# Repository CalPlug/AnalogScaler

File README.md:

# AnalogScaler
This circuit uses two quad operational amplifiers to scale a bi-polar input signal to be sampled by a 0-3.3V ADC that is common on microcontrollers

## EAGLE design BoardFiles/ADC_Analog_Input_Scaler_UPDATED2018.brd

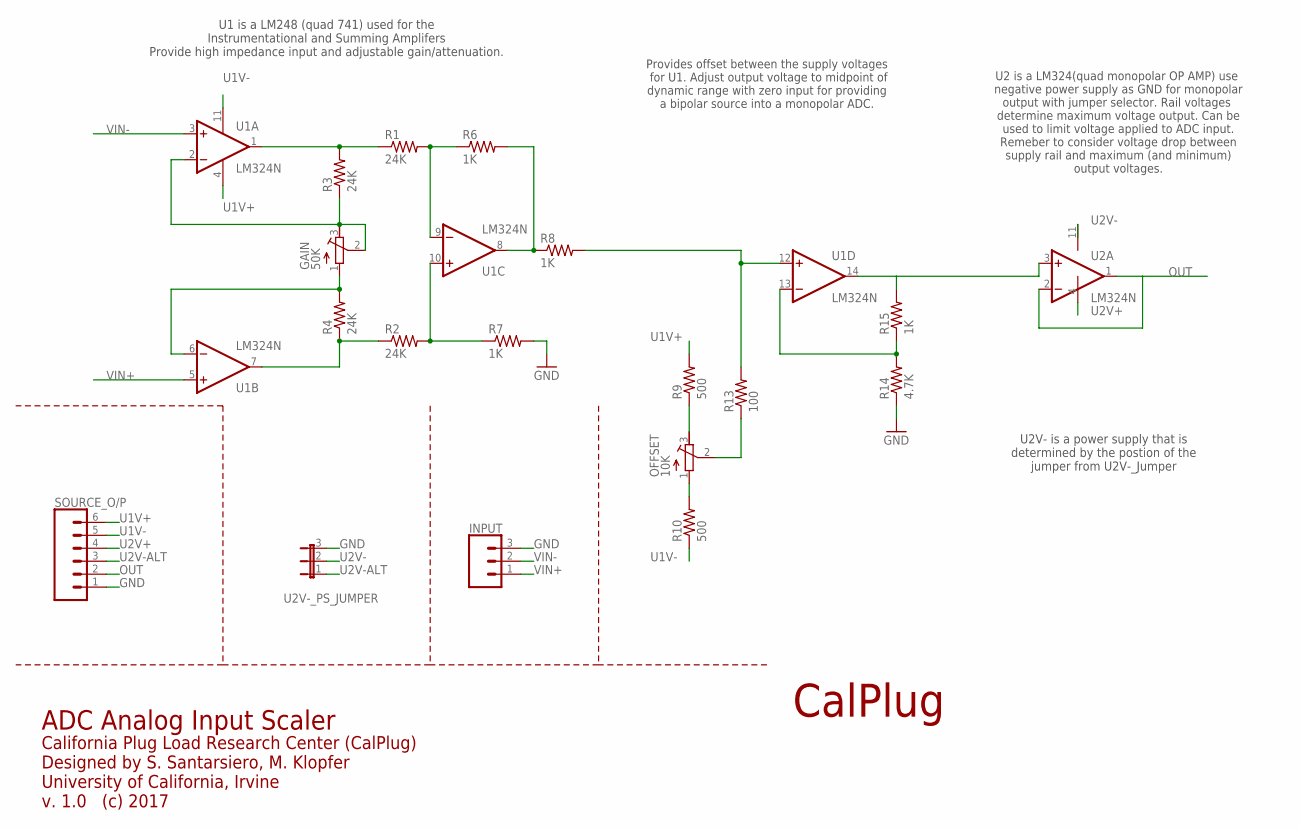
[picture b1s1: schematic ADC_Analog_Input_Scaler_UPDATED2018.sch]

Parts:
GAIN: 50K; RTRIM3296W
INPUT: CONN_03; 1X03
OFFSET: 10K; RTRIM3296W
R1, R2, R3, R4: 24K; R1210
R6, R7, R8, R15: 1K; R1210
R9, R10: 500; R1206
R13: 100; R1210
R14: 4.7K; R1210
SOURCE_O/P: CONN_06LOCK; 1X06_LOCK
U1, U2: LM324N; DIL14
U2V-_PS_JUMPER: JP2E; JP2

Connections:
GND: INPUT.3, R7.2, R14.1, SOURCE_O/P.1, U2V-_PS_JUMPER.3
unnamed: GAIN.1 (A), R4.2, U1.6 (-IN)
unnamed: R1.1, R3.2, U1.1 (OUT)
unnamed: R2.1, R4.1, U1.7 (OUT)
unnamed: R1.2, R6.1, U1.9 (-IN)
unnamed: OFFSET.1 (A), R10.2
unnamed: R6.2, R8.1, U1.8 (OUT)
unnamed: R2.2, R7.1, U1.10 (+IN)
unnamed: OFFSET.3 (E), R9.1
unnamed: GAIN.2 (S), GAIN.3 (E), R3.1, U1.2 (-IN)
unnamed: R8.2, R13.2, U1.12 (+IN)
unnamed: OFFSET.2 (S), R13.1
unnamed: R15.2, U1.14 (OUT), U2.3 (+IN)
unnamed: R14.2, R15.1, U1.13 (-IN)
OUT: SOURCE_O/P.2, U2.1 (OUT), U2.2 (-IN)
U1V+: R9.2, SOURCE_O/P.6, U1.4 (V+)
U1V-: R10.1, SOURCE_O/P.5, U1.11 (V-)
U2V+: SOURCE_O/P.4, U2.4 (V+)
U2V-: U2.11 (V-), U2V-_PS_JUMPER.2
U2V-ALT: SOURCE_O/P.3, U2V-_PS_JUMPER.1
VIN+: INPUT.1, U1.5 (+IN)
VIN-: INPUT.2, U1.3 (+IN)

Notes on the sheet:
U1 is a LM248 (quad 741) used for the Instrumentational and Summing Amplifers Provide high impedance input and adjustable gain/attenuation.
U2 is a LM324(quad monopolar OP AMP) use negative power supply as GND for monopolar output with jumper selector. Rail voltages determine maximum voltage output. Can be used to limit voltage applied to ADC input. Remeber to consider voltage drop between supply rail and maximum (and minimum) output v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
U2V- is a power supply that is determined by the postion of the jumper from U2V-_Jumper
Provides offset between the supply voltages for U1. Adjust output voltage to midpoint of dynamic range with zero input for providing a bipolar source into a monopolar ADC.
CalPlug
California Plug Load Research Center (CalPlug) Designed by S. Santarsiero, M. Klopfer University of California, Irvine v. 1.0 (c) 2017
ADC Analog Input Scaler

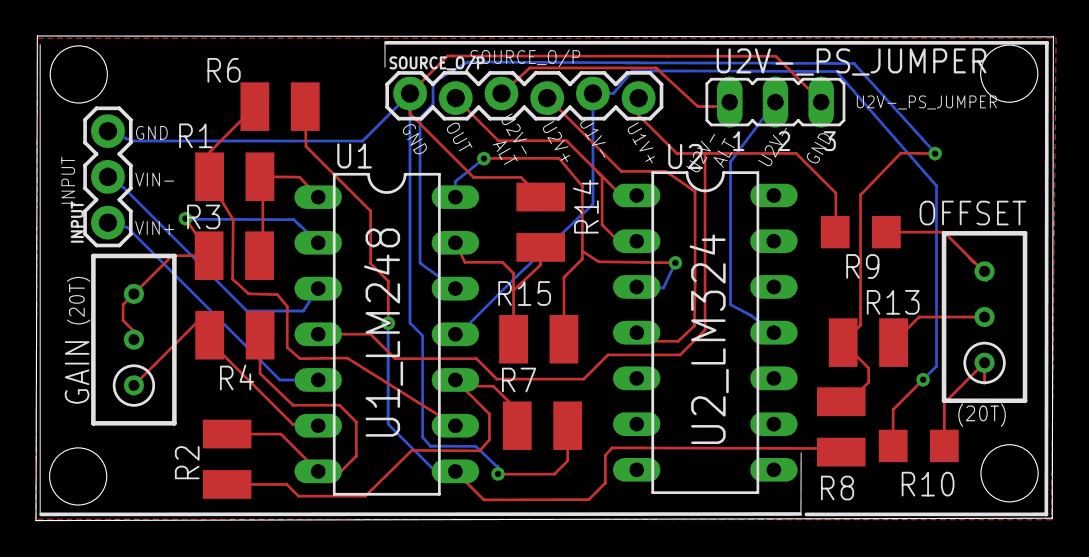
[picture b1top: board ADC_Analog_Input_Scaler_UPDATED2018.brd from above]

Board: 2 copper layers, 56.5 x 26.9 mm, 19 parts (0 on the bottom side), 22 nets.

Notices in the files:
parts and their libraries:
SparkFun-Connectors: Licensing: Creative Commons ShareAlike 4.0 International - https://creativecommons.org/licenses/by-sa/4.0
